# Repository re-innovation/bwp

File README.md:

# BWP

## Pre-requisites

* Install the Arduino IDE 1.6.6 or later
** Windows & Mac users may find a download link here: https://www.arduino.cc/en/Main/Software
** Major Linux distros carry it in their software repositories, or the link above may be used
** Install ''AccelStepper'' library.
** Install ''Mutila'' library, link: https://github.com/matthewg42/Mutila 

## Building Using the Arduino IDE

This method is preferred on Windows and for casual users who just want to build and use the project.

* Open Arduino IDE 
* Open firmware/firmware.ino
* Set the board to "Arduino Nano" (under the Tools -> Board menu)
* Connect Nano 
* Click the Upload button on the tool bar

## Using make on Linux

This alternative build system may also be used. It is an alternative to using the Arduino IDE and may be preferred by some users. 

* Intall the Arduino-Makefile system: https://github.com/sudar/Arduino-Makefile
* Edit the arduino.mk file and set the include line to point at where you installed Arduino-Makefile (or set the ARDUINO_MAKEFILE environment variable)
* In a shell, from the ''firmware'' directory, use the command "make upload" to build and install the code

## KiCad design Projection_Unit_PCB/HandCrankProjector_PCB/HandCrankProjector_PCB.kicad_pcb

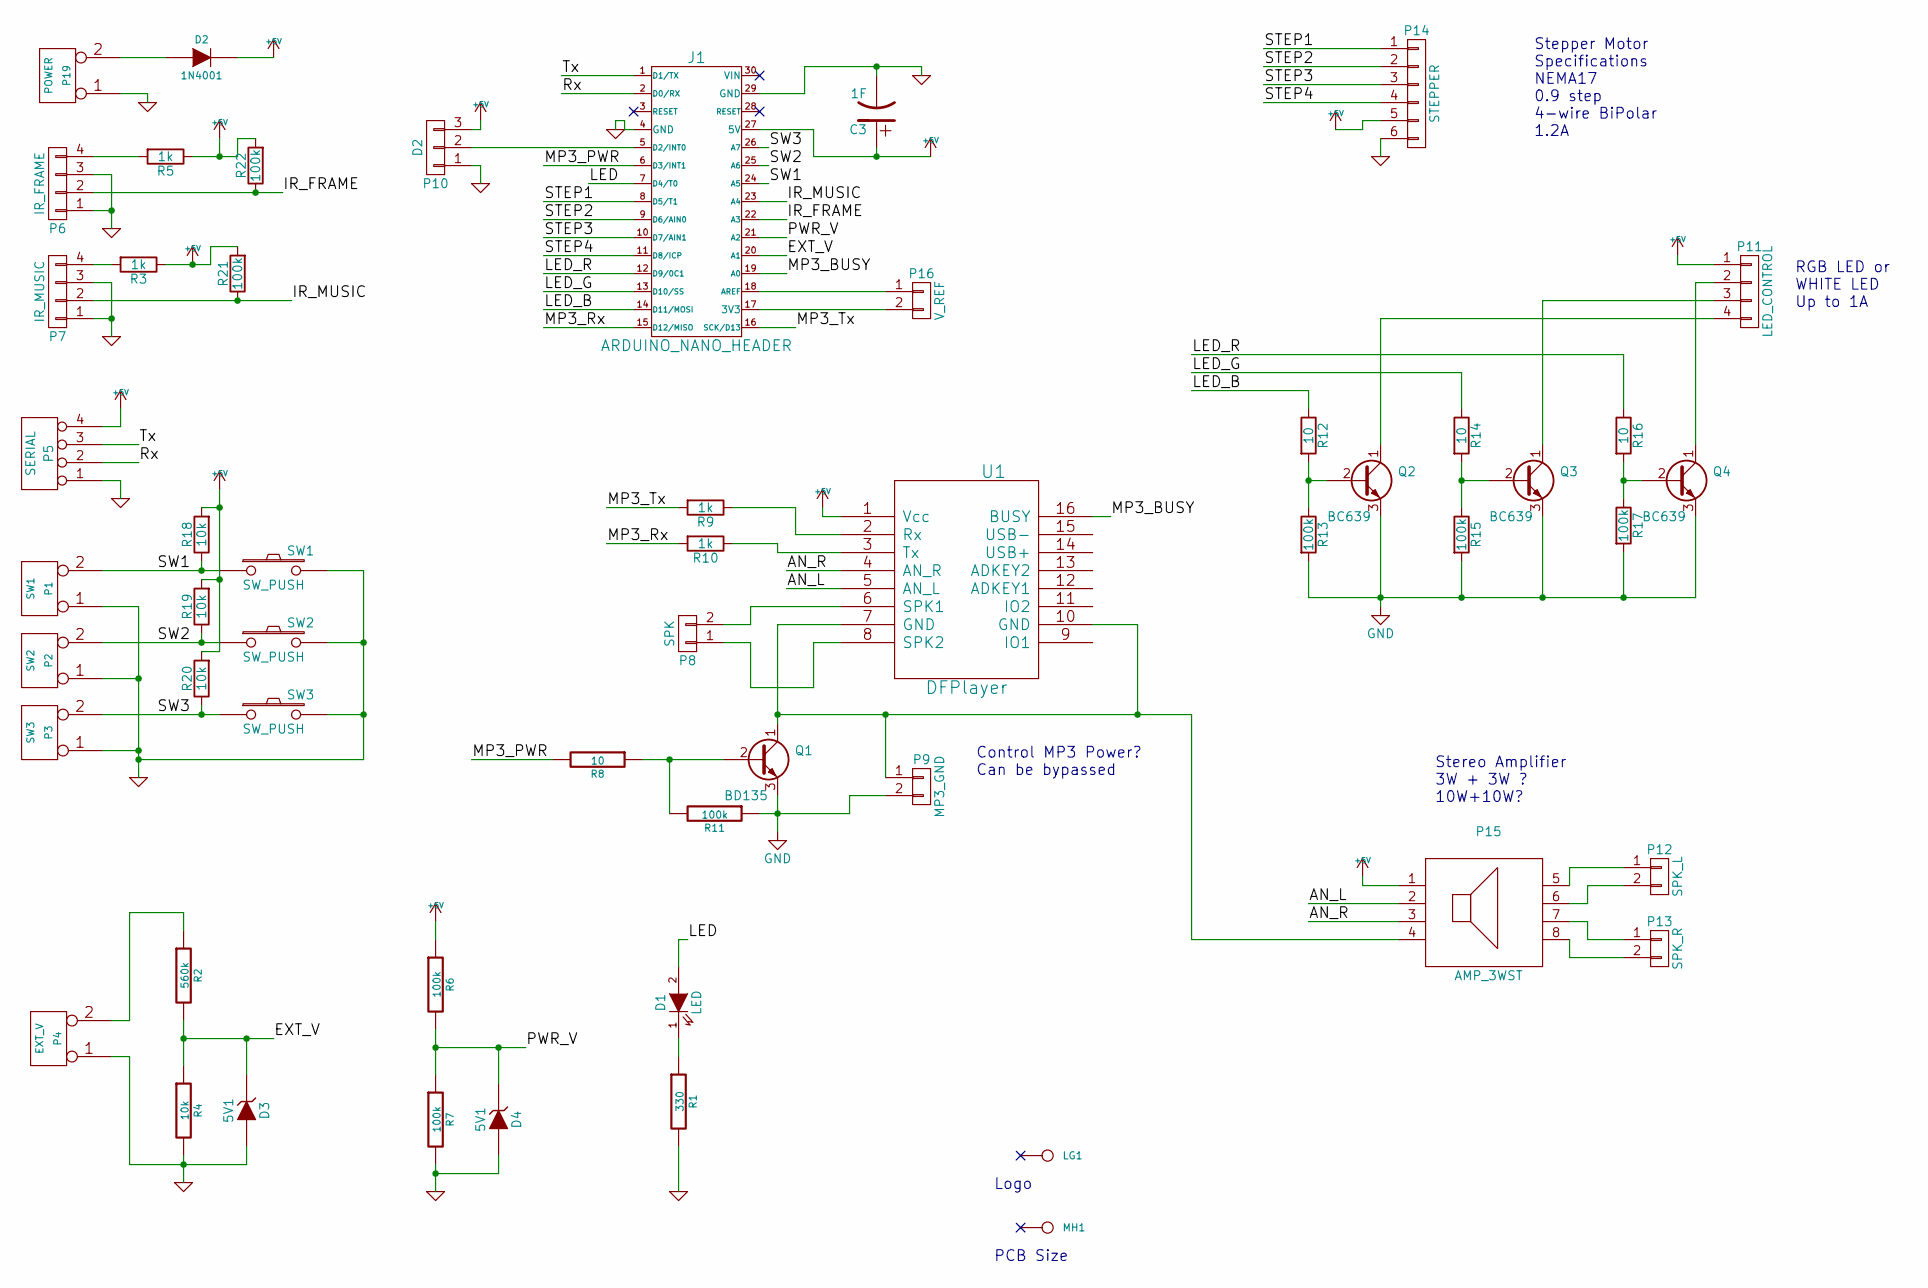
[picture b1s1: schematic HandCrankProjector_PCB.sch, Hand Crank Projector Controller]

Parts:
C3: 1F; C_1F_SuperCap; Manufacturer Part No Value
D1: LED; TH_LED-5MM_larg_pad
D2: 1N4001; TH_Diode_1
D3, D4: 5V1; TH_Diode_1
J1: ARDUINO_NANO_HEADER; NANO_DIP_30_600
LG1: CONN_1; reinnovation_logo_15mm
MH1: CONN_1; PCB_75x100mm
P1: SW1; SIL-2_large_hole
P2: SW2; SIL-2_large_hole
P3: SW3; SIL-2_large_hole
P4: EXT_V; SIL-2_screw_terminal
P5: SERIAL; SIL-4_Grove_SIL
P6: IR_FRAME; SIL-4_Grove_SIL
P7: IR_MUSIC; SIL-4_Grove_SIL
P8: SPK; SIL-2_screw_terminal
P9: MP3_GND; SM_2_SLDR_JMP
P10: D2; Pin_Header_Straight_1x03
P11: LED_CONTROL; SIL-4_Grove_SCREW
P12: SPK_L; SIL-2_screw_terminal
P13: SPK_R; SIL-2_screw_terminal
P14: STEPPER; TH_6W_SCREW_TERM
P15: AMP_3WST; TH_PAM8403_Amp
P16: V_REF; SM_2_SLDR_JMP
P19: POWER; SIL-2_screw_terminal; Manufacturer Part No Value
Q1: BD135; TO92-ECB_large_pad_BC639
Q2, Q3, Q4: BC639; TO92-ECB_large_pad_BC639
R1: 330; TH_Resistor_1; Manufacturer Part No Value
R2: 560k; TH_Resistor_1; Manufacturer Part No Value
R3, R5, R9, R10: 1k; TH_Resistor_1
R4: 10k; TH_Resistor_1; Manufacturer Part No Value
R6, R7, R11: 100k; TH_Resistor_1; Manufacturer Part No Value
R8: 10; TH_Resistor_1; Manufacturer Part No Value
R12, R14, R16: 10; TH_Resistor_1
R13, R15, R17, R21, R22: 100k; TH_Resistor_1
R18, R19, R20: 10k; TH_Resistor_1
SW1, SW2, SW3: SW_PUSH; SW_PUSH_single_pins
U1: DFPlayer; TH_DFPlayer_Mini

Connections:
+5V: C3.1, D2.2 (K), J1.27 (5V), P5.4, P10.3, P11.1, P14.5, P15.1, R3.1, R5.1, R6.1, R18.2, R19.2, R20.2, R21.2, R22.2, U1.1 (Vcc)
/AN_L: P15.2, U1.5 (AN_L)
/AN_R: P15.3, U1.4 (AN_R)
/EXT_V: D3.2 (K), J1.20 (A1), R2.2, R4.1
/IR_FRAME: J1.22 (A3), P6.2, R22.1
/IR_MUSIC: J1.23 (A4), P7.2, R21.1
/LED: D1.2 (A), J1.7 (D4/T0)
/LED_B: J1.14 (D11/MOSI), R12.1
/LED_G: J1.13 (D10/SS), R14.1
/LED_R: J1.12 (D9/0C1), R16.1
/MP3_BUSY: J1.19 (A0), U1.16 (BUSY)
/MP3_PWR: J1.6 (D3/INT1), R8.2
/MP3_Rx: J1.15 (D12/MISO), R10.2
/MP3_Tx: J1.16 (SCK/D13), R9.2
/PWR_V: D4.2 (K), J1.21 (A2), R6.2, R7.1
/Rx: J1.2 (D0/RX), P5.2
/STEP1: J1.8 (D5/T1), P14.1
/STEP2: J1.9 (D6/AIN0), P14.2
/STEP3: J1.10 (D7/AIN1), P14.3
/STEP4: J1.11 (D8/ICP), P14.4
/SW1: J1.24 (A5), P1.2 (PM), R18.1, SW1.1
/SW2: J1.25 (A6), P2.2 (PM), R19.1, SW2.1
/SW3: J1.26 (A7), P3.2 (PM), R20.1, SW3.1
/Tx: J1.1 (D1/TX), P5.3
GND: C3.2, D3.1 (A), D4.1 (A), J1.4 (GND), J1.29 (GND), P1.1, P2.1, P3.1, P4.1, P5.1, P6.1, P6.3, P7.1, P7.3, P9.2, P10.1, P14.6, P19.1, Q1.3 (E), Q2.3 (E), Q3.3 (E), Q4.3 (E), R1.2, R4.2, R7.2, R11.1, R13.2, R15.2, R17.2, SW1.2, SW2.2, SW3.2
unnamed: D1.1 (K), R1.1
unnamed: D2.1 (A), P19.2 (PM)
unnamed: J1.5 (D2/INT0), P10.2
unnamed: J1.17 (3V3), P16.2
unnamed: J1.18 (AREF), P16.1
unnamed: P4.2 (PM), R2.1
unnamed: P6.4, R5.2
unnamed: P7.4, R3.2
unnamed: P8.1, U1.8 (SPK2)
unnamed: P8.2, U1.6 (SPK1)
unnamed: P11.2, Q4.1 (C)
unnamed: P11.3, Q3.1 (C)
unnamed: P11.4, Q2.1 (C)
unnamed: P12.1, P15.5
unnamed: P12.2, P15.6
unnamed: P13.1, P15.7
unnamed: P13.2, P15.8
unnamed: P9.1, P15.4, Q1.1 (C), U1.7 (GND), U1.10 (GND)
unnamed: Q1.2 (B), R8.1, R11.2
unnamed: Q2.2 (B), R12.2, R13.1
unnamed: Q3.2 (B), R14.2, R15.1
unnamed: Q4.2 (B), R16.2, R17.1
unnamed: R9.1, U1.2 (Rx)
unnamed: R10.1, U1.3 (Tx)

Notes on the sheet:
PCB Size
Stepper Motor Specifications NEMA17 0.9 step 4-wire BiPolar 1.2A
Stereo Amplifier 3W + 3W ? 10W+10W?
Control MP3 Power? Can be bypassed
RGB LED or WHITE LED Up to 1A
Logo

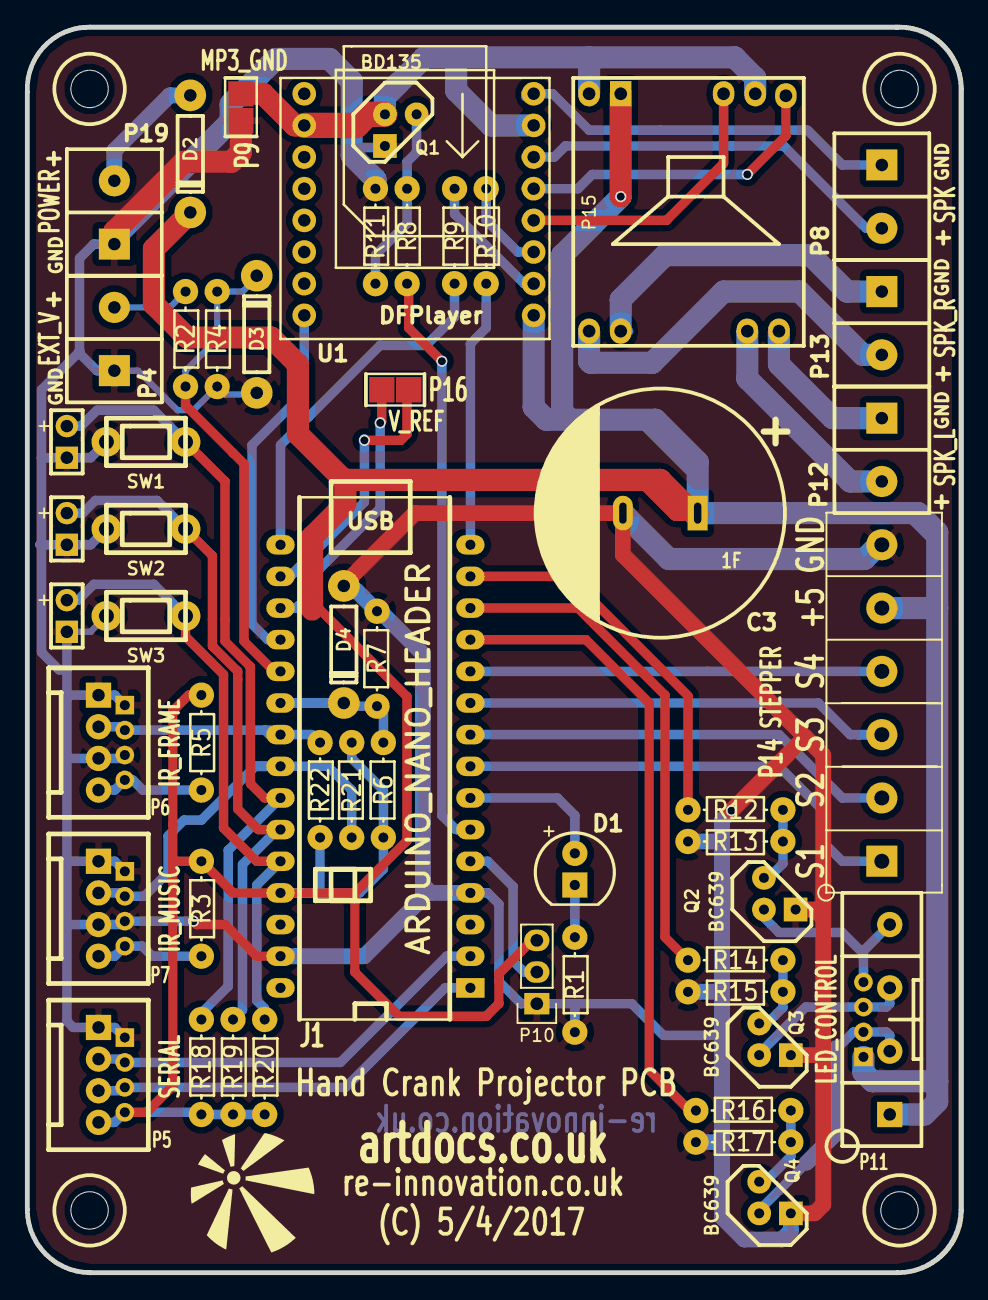
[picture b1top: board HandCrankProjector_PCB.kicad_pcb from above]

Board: 2 copper layers, 74.9 x 99.9 mm, 55 parts (0 on the bottom side), 49 nets.

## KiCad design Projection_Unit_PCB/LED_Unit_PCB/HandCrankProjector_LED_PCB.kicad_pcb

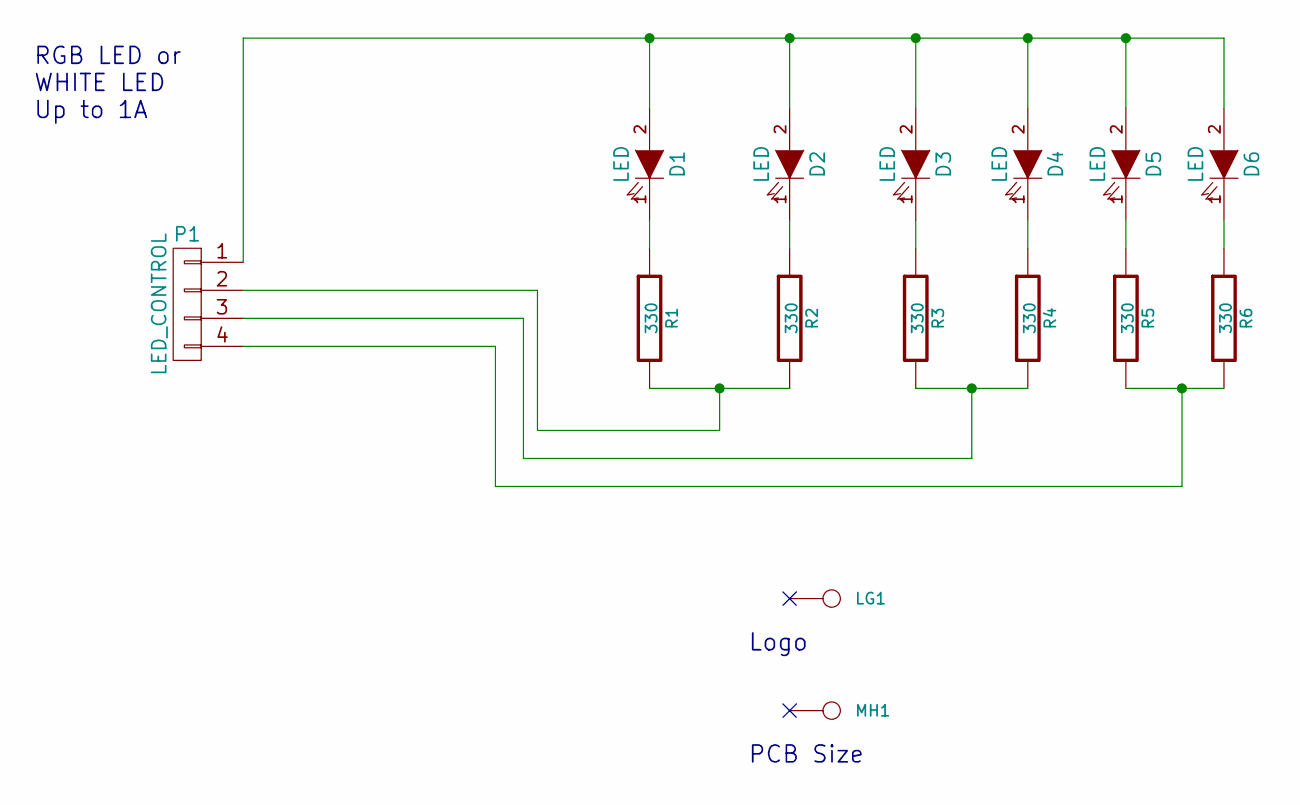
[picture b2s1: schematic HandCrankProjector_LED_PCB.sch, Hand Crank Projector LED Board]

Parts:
D1, D2, D3, D4, D5, D6: LED; TH_LED-5MM_larg_pad; Manufacturer Part No Value
LG1: CONN_1; reinnovation_logo_15mm
MH1: CONN_1; PCB_50x50mm
P1: LED_CONTROL; SIL-4_Grove_SCREW
R1, R2, R3, R4, R5, R6: 330; TH_Resistor_1; Manufacturer Part No Value

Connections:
unnamed: D1.1 (K), R1.1
unnamed: D1.2 (A), D2.2 (A), D3.2 (A), D4.2 (A), D5.2 (A), D6.2 (A), P1.1
unnamed: D2.1 (K), R2.1
unnamed: D3.1 (K), R3.1
unnamed: D4.1 (K), R4.1
unnamed: D5.1 (K), R5.1
unnamed: D6.1 (K), R6.1
unnamed: P1.2, R1.2, R2.2
unnamed: P1.3, R3.2, R4.2
unnamed: P1.4, R5.2, R6.2

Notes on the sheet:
PCB Size
RGB LED or WHITE LED Up to 1A
Logo

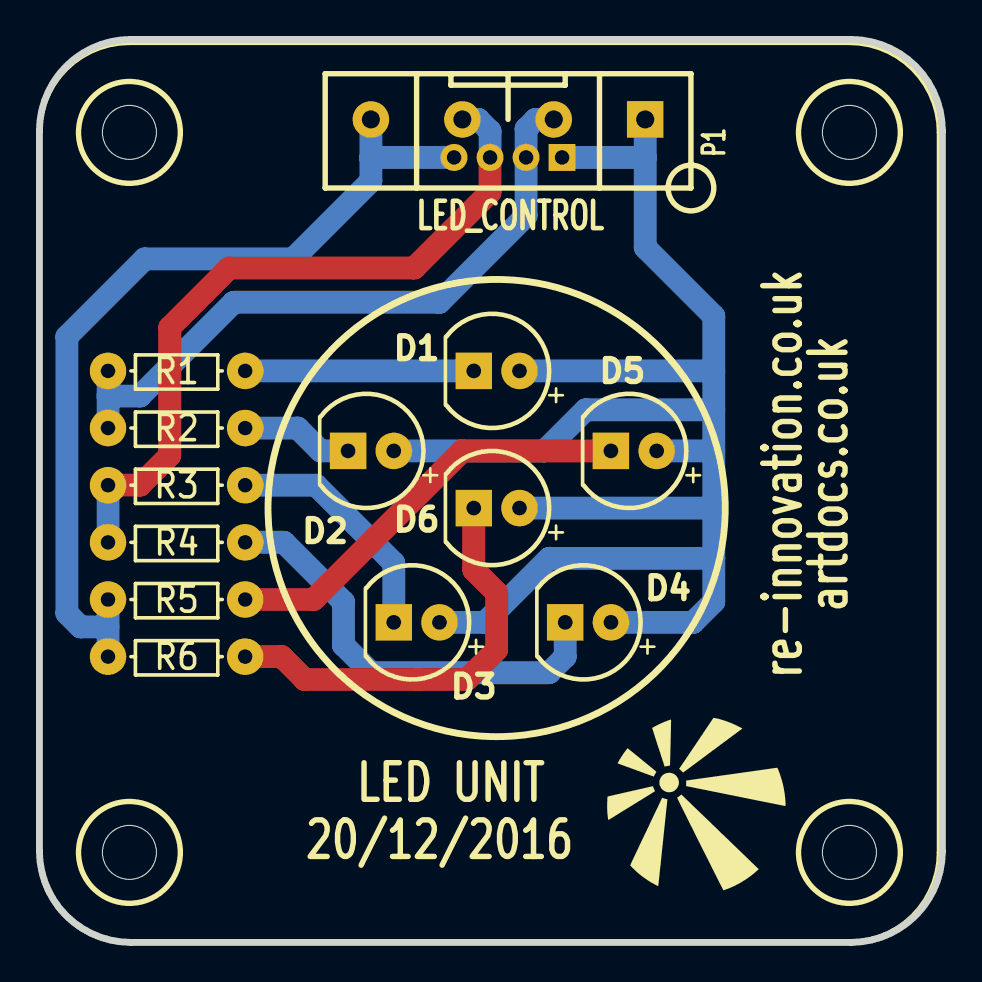
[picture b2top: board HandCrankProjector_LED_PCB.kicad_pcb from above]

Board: 2 copper layers, 50.2 x 50.2 mm, 15 parts (0 on the bottom side), 10 nets.

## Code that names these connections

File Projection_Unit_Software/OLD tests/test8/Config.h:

#pragma once

#define MP3_RX_PIN                  6
#define MP3_TX_PIN                  5
#define MP3_BUSY_PIN                10
#define MP3_VOLUME                  10
#define MP3_TRACK_ZERO              200
#define MP3_TRACK_POINT             210
#define MP3_TRACK_HOURS             211
#define MP3_TRACK_MINUTES           212
#define MP3_TRACK_SECONDS           213
#define MP3_TRACK_NUMBER_OF_USES    214
#define MP3_TRACK_AVERAGE_RUNTIME   215
#define MP3_TRACK_TOTAL_RUNTIME     216

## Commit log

2016-12-16 Initial commit
    Proof of concept test code for frame synchronisation.
2016-12-22 new makefile stuff ; slow it down
2016-12-22 actually leave it as proj demo
2016-12-22 measure pulses with length from reflection sensor
2016-12-22 Audio sync mark reading
2016-12-22 rename 4 2
2016-12-22 correct docs
2016-12-22 mp3 proof of concept
2016-12-22 shutter + audiosync + mp3 playback
2016-12-23 first hamming implementation
2016-12-23 how to draw with svg library
2016-12-23 hamming code generator runs
2016-12-28 start implementing as distinct classes
2016-12-28 add class for stepper motor control
2016-12-30 refactor into Projector class
2016-12-30 rename some constants, remove unused
2016-12-30 debugging and manual test settings
2017-01-02 audio mark reading raw bits
    Populates buffer ok (tested with TESTMODE and a pot, so
    would be good to test with actual device). Still need to
    implement hamming code de-coding routine.
2017-01-03 make codes 8/12 length
2017-01-04 correct bit order
2017-01-04 add desktop hamming decode test
2017-01-04 rename some functions, better comments
2017-01-04 add description doc
2017-01-04 reset after read
2017-01-04 change encoding to narrow/wide bars
    We used to trigger on any state transition, and use the previous
    length as a 0 or 1, but this is a problem with an even number
    of bits, as the last bit will not have a visible boundary at
    it's end, and if one is added, that starts a new bit...
    So I changed the encoding to be short white blob = 0, long white
    blob = 1. This should also make the demodulation code easier to
2017-01-04 add direction of filnm indicator
2017-01-04 Implement new stripe format
    Thin white stripes mean zero, thicker ones mean one. The
    values AUDIO_SYNC_ZERO_MIN_LEN, AUDIO_SYNC_ONE_MIN_LEN,
    AUDIO_SYNC_ONE_MAX_LEN need to be set according to the size
    of the white stripes in stepper half-steps.
2017-01-04 reset start counter on both edges
2017-01-04 Put speed back up to proper speed
2017-01-05 MP3-only debugging option
2017-01-05 embiggen codes slightly
2017-01-05 don't forget to init Mp3 device
2017-01-05 tweaks/calibration for new code size
2017-01-05 test7 to figure wrong track playing
    Turns out should be usig the PlayTf command, not Play for the DFPlayer
    Mini device.
2017-01-05 compact (faster) debug messages
2017-01-05 tweaks for test rig
2017-01-05 fixed frame sync done
2017-01-10 add audio for diagnostics
2017-01-10 saying numbers test
2017-01-10 tweak layout
2017-01-10 Mp3Player numeric readout
2017-01-10 document new reqs
2017-01-10 start implementing modes and system objects
2017-01-10 NormalMode skeleton added
2017-01-10 mode switching
2017-01-10 run projector in NormalMode
2017-01-11 add new audio for singular time periods
2017-01-11 moar audio
2017-01-16 move numeric playing into Mutila library and use
2017-01-16 add muting and shutter on/off
2017-01-16 add SetButton
2017-01-16 remove TESTMODE
2017-01-16 stop audio on brownout / mode change
2017-01-16 new audio files
2017-01-16 diagnostic sub mode: frame sync adjust
2017-01-16 update notes
2017-01-18 don't forget to init DFPReader object
2017-01-18 not muted by default
2017-01-18 say which mode we're in
2017-01-18 add manual feed
2017-01-18 Rename buttons to match circuit board labels
2017-01-18 untested volume control mode
2017-01-18 New pinout for prototype 2
2017-01-18 rename constants for button pins
2017-01-18 correct button config
2017-02-03 MP3 check on start; xtra init delay
2017-02-03 update TODO docs
2017-02-03 Mp3Player is now derived from DFPReader
2017-02-03 split verbose debugging
2017-02-03 turn on all RGB channels for shutter
2017-02-03 add debugging mode start/stop
2017-02-03 xtra debug; SW2 -> SW3
2017-02-03 SW2 -> SW3
2017-02-03 volume adjustment up and down7
2017-02-03 testing tweaks
2017-02-03 enable loadsa debug
2017-02-03 plan today's work
2017-02-03 reset buttonstate / closeShutter
2017-02-03 change testing values
2017-02-03 new sound for vol adj mode
2017-02-03 reinstate shutterless manual feed
2017-02-03 ugly work around for delay b4 volume set
2017-02-03 clean up init
2017-02-03 debug frame sync
2017-02-06 try different init ordering
2017-02-06 prioritize day's work
2017-02-06 remove special DBV macros
2017-02-06 re-order diagnostic sub-modes
2017-02-06 debug tweak
2017-02-06 tuning and testing sensors
2017-02-06 test volume
2017-02-06 persistent settings / stat recording
2017-02-06 implement diagnostic readouts
2017-02-06 shut up when ending readout modes
2017-02-06 correct VIN settings
2017-02-06 more complete runtime
2017-02-06 implement average readout
2017-02-06 document final changes
2017-02-06 reduce debug verbosity
2017-02-06 fix warning: non-void function return
2017-02-06 frame offset persistent
2017-02-06 fix arduino build / add dep docs
2017-05-11 Explicitly set stepper control LOW on brownout
2017-05-12 fix volume after brownout
2017-05-12 explicitly set vomume in diagnostic mode
2017-05-12 tweak audio mark detection values
2017-05-12 fix volume setting part 3
2017-05-12 Watchdog; volume fix 3; heartbeat
    Watchdog timer added (500ms)
    Final (?!) fix for volume problem (explitit set before playing every
    sample). This is somewhat giving up, but it seems like the DFPlayer Mini
    is resetting at random times or something like that and there isn't time
    to full investigate, or the potential to fix the hardware, so explicity
    setting the volume every time seems like a reasonale compromise.
2017-05-12 add utility to post-process debug output
2017-05-12 more heartbeat state
2017-05-12 update readme and convert to rst
2017-06-21 Add generic audio files
    I had moved these files to the Mutila library when I moved the DFReader
    class there, but in hindsight,it's better to have a copy here also to
    make the preparation of the SD card easier.
2017-06-22 make a utility to help debug frame calc
2017-06-22 show diff as well
2017-06-22 Minimum value detection
    We have noise on the film (numbers) which are adding noise to the frame
    detection. However, the noise is generally in the 300-800 range, so we
    will only trigger a frame if the low end of the leading edge is below
    some threshold (set with SHUTTER_SYNC_LOW_TRIGGER). It works well!
2017-07-11 Allow some slippage during long mark (1) read
    The film seems to slip sometimes, resulting in marks being seen as being
    too long. We can reduce the impact of this by allowing very long marks
    for the longer (1) values, si I increased the long mark max length to be
    very long. Won't catch slippage in shorter marks, but there's no easy
    fix for that in software.
2017-07-11 add description of this branch in TODO
2017-07-11 add setting for audio mark count
2017-07-11 add audio mark count to runtime settings
2017-07-11 add last audio setting
2017-07-11 add audio mark failed read sequencing
2017-07-11 trigger on audio mark timeout
2017-07-11 let magic protocol handle invalid values
2017-07-11 better debugging output, reset more thoroughly
2017-07-11 handle partial reads better
2017-07-11 make partial audio reads work
2017-07-11 debug audio even in non-debug mode
2017-07-12 be explicit about levels
2017-07-12 don't forget to turn the amp on and off
2017-07-25 Don't enter diagnostic mode when browned out
    This fixes a subtle and occasional problem as the power in the storage
    cap dies... on occasion, as the last charge dissipates, the mode button
    input triggers (goes LOW), causing the unit to enter diagnostic mode...
    If the unit is re-powered between this time and the unit truly powering
    off, it will stay in diagnostic mode and appear not to work (as
    diagnostic mode starts with "manual feed", which does nothing until a
2017-07-25 change magic for new version
2018-09-13 Adding all design files
    BIG update
2019-12-07 cleanup obsolete files, fix bad location of files from master branch
2019-12-07 update identifiers of standard track names for recent Mutila version
2019-12-07 update TODO list for new specs
2019-12-07 fix integer overflow bug when calculating number of minutes
2020-01-24 add new audio tracks
2020-01-24 bundle of solar-battery changes
2020-01-24 saner range for crank speed setting
2020-01-24 update docs & comments
2020-01-24 make Heartbeat a compile time option Config.h/ENABLE_HEARTBEAT
2020-03-15 fix for crank speed wrap-around
